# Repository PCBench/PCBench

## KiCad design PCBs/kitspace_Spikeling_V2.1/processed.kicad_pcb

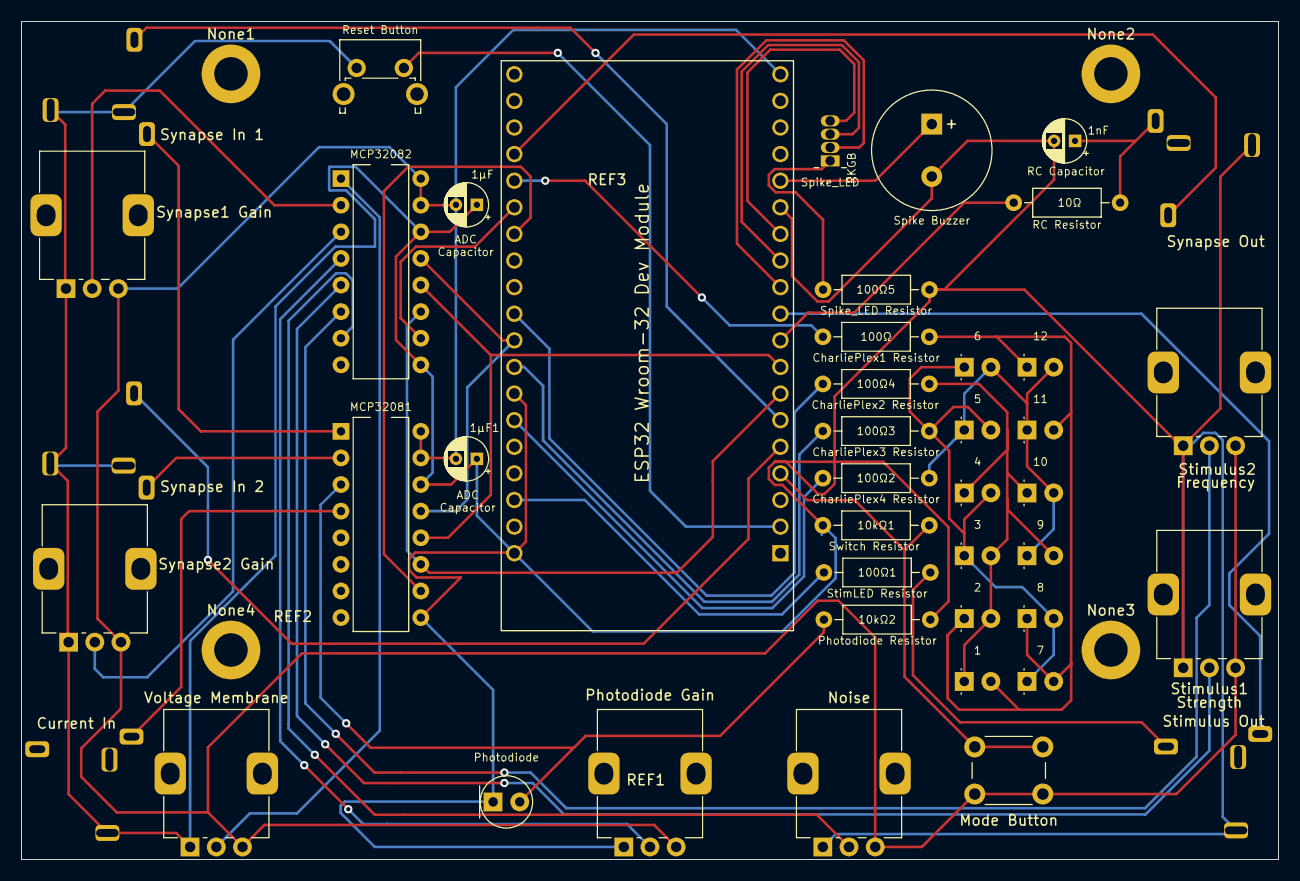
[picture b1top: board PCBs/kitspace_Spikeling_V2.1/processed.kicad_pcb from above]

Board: 2 copper layers, 120.0 x 80.0 mm, 51 parts (0 on the bottom side), 41 nets.

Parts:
1: D2; LED_D3.0mm
1nF: C3; CP_Radial_D4.0mm_P2.00mm
1μF, 1μF1: 1 μF; CP_Radial_D4.0mm_P2.00mm
2: D3; LED_D3.0mm
3: D4; LED_D3.0mm
4: D5; LED_D3.0mm
5: D6; LED_D3.0mm
6: D7; LED_D3.0mm
7: D8; LED_D3.0mm
8: LED; LED_D3.0mm
9: D10; LED_D3.0mm
10: D11; LED_D3.0mm
10kΩ1: R5; R_Axial_DIN0207_L6.3mm_D2.5mm_P10.16mm_Horizontal
10kΩ2: R2; R_Axial_DIN0207_L6.3mm_D2.5mm_P10.16mm_Horizontal
10Ω: R1; R_Axial_DIN0207_L6.3mm_D2.5mm_P10.16mm_Horizontal
11: D12; LED_D3.0mm
12: D13; LED_D3.0mm
100Ω: R6; R_Axial_DIN0207_L6.3mm_D2.5mm_P10.16mm_Horizontal
100Ω1: R3; R_Axial_DIN0207_L6.3mm_D2.5mm_P10.16mm_Horizontal
100Ω2: R9; R_Axial_DIN0207_L6.3mm_D2.5mm_P10.16mm_Horizontal
100Ω3: R8; R_Axial_DIN0207_L6.3mm_D2.5mm_P10.16mm_Horizontal
100Ω4: R7; R_Axial_DIN0207_L6.3mm_D2.5mm_P10.16mm_Horizontal
100Ω5: R4; R_Axial_DIN0207_L6.3mm_D2.5mm_P10.16mm_Horizontal
Current In: J4; Spikeling Audio Jack 3.5mm
ESP32 Wroom-32 Dev Module: ESP32-DEVKITC-32D; MODULE_ESP32-DEVKITC-32D
MCP32081: MCP32082; DIP-16_W7.62mm
MCP32082: MCP32084; DIP-16_W7.62mm
Mode Button: SW1; SW_PUSH_6mm_H13mm
Noise: RV4; Spikeling Potentiometer
None1, None3, None4: MountingHole_3.2mm_M3_DIN965_Pad
None2: MountingHole_M3; MountingHole_3.2mm_M3_DIN965_Pad
Photodiode: D1; LED_D5.0mm
Photodiode Gain: RV5; Spikeling Potentiometer
REF1: Spikeling_neuron; Spikeling_Photoreceptor
REF2: Spikeling_neuron; Spikeling_Electrode
REF3: Spikeling_neuron; Spikeling_Neuron
Reset Button: SW2; Spikeling reset button
Spike Buzzer: BZ1; Buzzer_11.5x9.5RM5
Spike_LED: RGB; LED_D5.0mm-4_RGB
Stimulus1: RV6; Spikeling Potentiometer
Stimulus2: RV7; Spikeling Potentiometer
Stimulus Out: J5; Spikeling Audio Jack 3.5mm
Synapse1 Gain: RV1; Spikeling Potentiometer
Synapse2 Gain: RV2; Spikeling Potentiometer
Synapse In 1: J2; Spikeling Audio Jack 3.5mm
Synapse In 2: J3; Spikeling Audio Jack 3.5mm
Synapse Out: J1; Spikeling Audio Jack 3.5mm
Voltage Membrane: RV3; Spikeling Potentiometer

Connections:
/00: ESP32 Wroom-32 Dev Module.33, MCP32082.10
/02: 100Ω.1, ESP32 Wroom-32 Dev Module.34
/04: ESP32 Wroom-32 Dev Module.32, MCP32081.10
/05: 100Ω4.1, ESP32 Wroom-32 Dev Module.29
/12: ESP32 Wroom-32 Dev Module.13, Spike_LED.4
/13: ESP32 Wroom-32 Dev Module.15, Spike Buzzer.1
/14: ESP32 Wroom-32 Dev Module.12, Spike_LED.3
/15: ESP32 Wroom-32 Dev Module.35, Synapse Out.T
/18: ESP32 Wroom-32 Dev Module.28, MCP32081.13, MCP32082.13
/19: 100Ω3.1, ESP32 Wroom-32 Dev Module.27
/21: 100Ω2.1, ESP32 Wroom-32 Dev Module.25
/22: 100Ω1.1, ESP32 Wroom-32 Dev Module.22
/25: 10Ω.1, ESP32 Wroom-32 Dev Module.9
/26: ESP32 Wroom-32 Dev Module.10, Stimulus Out.R
/27: ESP32 Wroom-32 Dev Module.11, Spike_LED.1
/32: ESP32 Wroom-32 Dev Module.7, MCP32081.11, MCP32082.11
/33: ESP32 Wroom-32 Dev Module.8, MCP32081.12, MCP32082.12
/34: ESP32 Wroom-32 Dev Module.5, Synapse In 2.T
/35: ESP32 Wroom-32 Dev Module.6, Synapse In 1.T
/39: 10kΩ1.1, ESP32 Wroom-32 Dev Module.4, Mode Button.1
/100: MCP32082.1, Voltage Membrane.2
/101: MCP32082.2, Synapse1 Gain.2
/102: MCP32082.3, Synapse2 Gain.2
/103: MCP32082.4, Photodiode Gain.2
/104: MCP32082.5, Stimulus1.2
/105: MCP32082.6, Stimulus2.2
/106: MCP32082.7, Noise.2
/200: MCP32081.1, Synapse In 1.R
/201: MCP32081.2, Synapse In 2.R
/202: 10kΩ2.1, MCP32081.3, Photodiode.2
/203: Current In.R, MCP32081.4
GNDREF: 1nF.2, 1μF.1, 1μF1.1, 10kΩ1.2, 10kΩ2.2, 100Ω5.1, Current In.S, ESP32 Wroom-32 Dev Module.14, ESP32 Wroom-32 Dev Module.20, ESP32 Wroom-32 Dev Module.26, MCP32081.9, MCP32081.14, MCP32082.9, MCP32082.14, Noise.1, Photodiode.1, Photodiode Gain.1, Reset Button.1, Spike Buzzer.2, Stimulus1.1, Stimulus2.1, Stimulus Out.S, Synapse1 Gain.1, Synapse2 Gain.1, Synapse In 1.S, Synapse In 2.S, Synapse Out.S, Voltage Membrane.1
unnamed: 1nF.1, 10Ω.2, Synapse Out.R
unnamed: 1.2, 2.1, 7.2, 8.1, 11.2, 12.1, 100Ω.2
unnamed: 1.1, 2.2, 3.2, 4.1, 9.2, 10.1, 100Ω4.2
unnamed: 3.1, 4.2, 5.2, 6.1, 7.1, 8.2, 100Ω3.2
unnamed: 5.1, 6.2, 9.1, 10.2, 11.1, 12.2, 100Ω2.2
unnamed: 100Ω5.2, Spike_LED.2
unnamed: 100Ω1.2, Stimulus Out.T
unnamed: ESP32 Wroom-32 Dev Module.2, Reset Button.2
VCC: 1μF.2, 1μF1.2, ESP32 Wroom-32 Dev Module.19, MCP32081.15, MCP32081.16, MCP32082.15, MCP32082.16, Mode Button.2, Noise.3, Photodiode Gain.3, Stimulus1.3, Stimulus2.3, Synapse1 Gain.3, Synapse2 Gain.3, Voltage Membrane.3

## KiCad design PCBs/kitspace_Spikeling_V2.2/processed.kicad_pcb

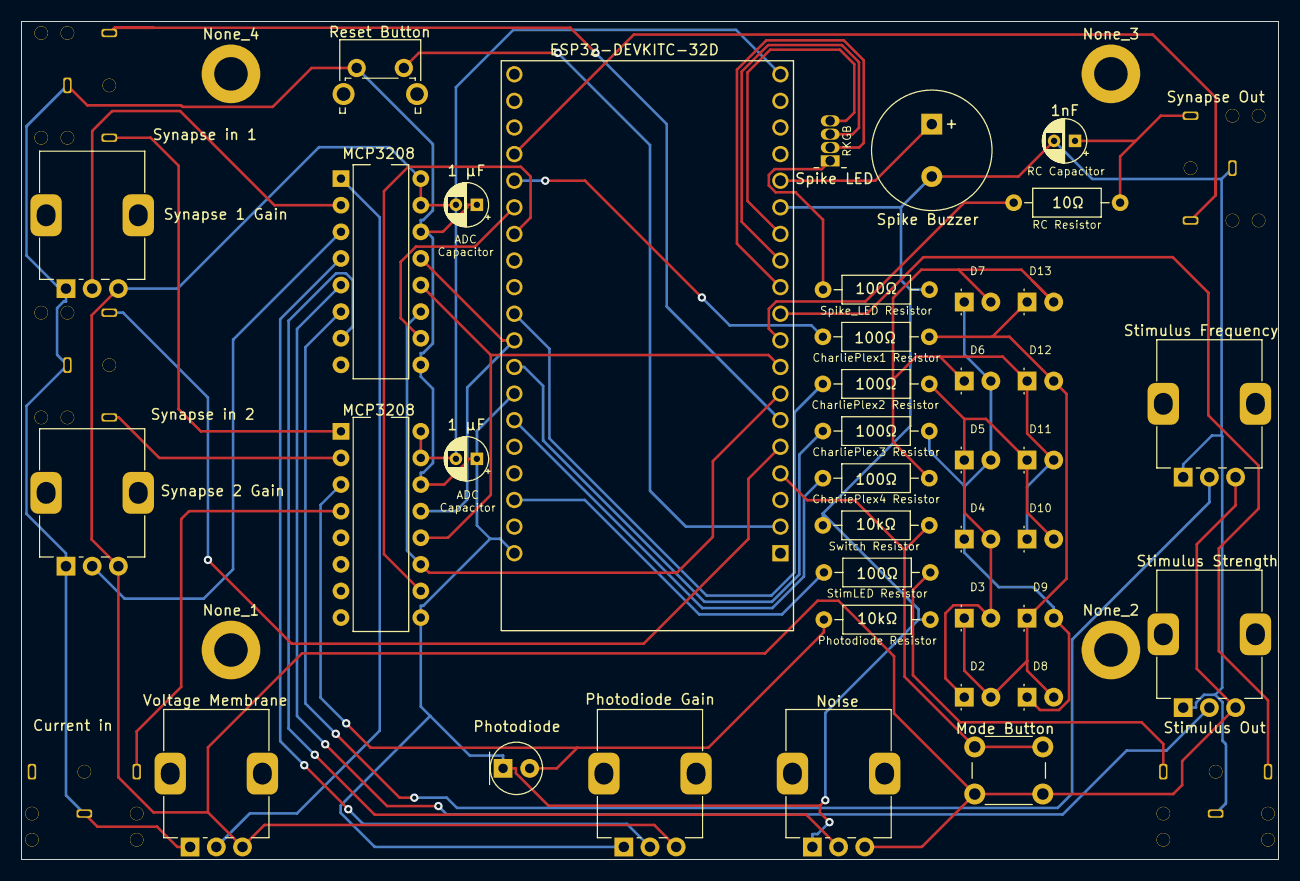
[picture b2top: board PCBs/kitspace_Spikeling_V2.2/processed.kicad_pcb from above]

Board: 2 copper layers, 120.0 x 80.0 mm, 48 parts (0 on the bottom side), 41 nets.

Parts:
BZ1: Spike Buzzer; Buzzer_11.5x9.5RM5
C1, C2: 1 μF; CP_Radial_D4.0mm_P2.00mm
C3: 1nF; CP_Radial_D4.0mm_P2.00mm
D1: Photodiode; LED_D5.0mm
D2: Mode1; LED_D3.0mm
D3: Mode2; LED_D3.0mm
D4: Mode3; LED_D3.0mm
D5: Mode4; LED_D3.0mm
D6: Mode5; LED_D3.0mm
D7: Mode6; LED_D3.0mm
D8: Mode7; LED_D3.0mm
D9: Mode8; LED_D3.0mm
D10: Mode9; LED_D3.0mm
D11: Mode10; LED_D3.0mm
D12: Mode11; LED_D3.0mm
D13: Mode12; LED_D3.0mm
D14: Spike LED; LED_D5.0mm-4_RGB
J1: Synapse Out; Spikeling Audio Jack 3.5mm
J2: Synapse in 1; Spikeling Audio Jack 3.5mm
J3: Synapse in 2; Spikeling Audio Jack 3.5mm
J4: Current in; Spikeling Audio Jack 3.5mm
J5: Stimulus Out; Spikeling Audio Jack 3.5mm
None_1, None_2, None_4: MountingHole_3.2mm_M3_DIN965_Pad
None_3: MountingHole_M3; MountingHole_3.2mm_M3_DIN965_Pad
R1: 10Ω; R_Axial_DIN0207_L6.3mm_D2.5mm_P10.16mm_Horizontal
R2, R5: 10kΩ; R_Axial_DIN0207_L6.3mm_D2.5mm_P10.16mm_Horizontal
R3, R4, R6, R7, R8, R9: 100Ω; R_Axial_DIN0207_L6.3mm_D2.5mm_P10.16mm_Horizontal
RV1: Synapse 1 Gain; Spikeling Potentiometer
RV2: Synapse 2 Gain; Spikeling Potentiometer
RV3: Voltage Membrane; Spikeling Potentiometer
RV4: Noise; Spikeling Potentiometer
RV5: Photodiode Gain; Spikeling Potentiometer
RV6: Stimulus Strength; Spikeling Potentiometer
RV7: Stimulus Frequency; Spikeling Potentiometer
SW1: Mode Button; SW_PUSH_6mm_H13mm
SW2: Reset Button; Spikeling reset button
U1: ESP32-DEVKITC-32D; MODULE_ESP32-DEVKITC-32D
U2, U3: MCP3208; DIP-16_W7.62mm

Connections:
/00: U1.33, U2.10
/02: R6.1, U1.34
/04: U1.32, U3.10
/05: R7.1, U1.29
/12: D14.4, U1.13
/13: BZ1.1, U1.15
/14: D14.3, U1.12
/15: J1.T, U1.35
/18: U1.28, U2.13, U3.13
/19: R8.1, U1.27
/21: R9.1, U1.25
/22: R3.1, U1.22
/25: R1.1, U1.9
/26: J5.R, U1.10
/27: D14.1, U1.11
/32: U1.7, U2.11, U3.11
/33: U1.8, U2.12, U3.12
/34: J3.T, U1.5
/35: J2.T, U1.6
/39: R5.1, SW1.1, U1.4
/100: RV3.2, U2.1
/101: RV1.2, U2.2
/102: RV2.2, U2.3
/103: RV5.2, U2.4
/104: RV6.2, U2.5
/105: RV7.2, U2.6
/106: RV4.2, U2.7
/200: J2.R, U3.1
/201: J3.R, U3.2
/202: D1.2, R2.1, U3.3
/203: J4.R, U3.4
GNDREF: BZ1.2, C1.1, C2.1, C3.2, D1.1, J1.S, J2.S, J3.S, J4.S, J5.S, R2.2, R4.1, R5.2, RV1.1, RV2.1, RV3.1, RV4.1, RV5.1, RV6.1, RV7.1, SW2.1, U1.14, U1.20, U1.26, U2.9, U2.14, U3.9, U3.14
unnamed: C3.1, J1.R, R1.2
unnamed: J5.T, R3.2
unnamed: D14.2, R4.2
unnamed: D2.2, D3.1, D8.2, D9.1, D12.2, D13.1, R6.2
unnamed: D2.1, D3.2, D4.2, D5.1, D10.2, D11.1, R7.2
unnamed: D4.1, D5.2, D6.2, D7.1, D8.1, D9.2, R8.2
unnamed: D6.1, D7.2, D10.1, D11.2, D12.1, D13.2, R9.2
unnamed: SW2.2, U1.2
VCC: C1.2, C2.2, RV1.3, RV2.3, RV3.3, RV4.3, RV5.3, RV6.3, RV7.3, SW1.2, U1.19, U2.15, U2.16, U3.15, U3.16

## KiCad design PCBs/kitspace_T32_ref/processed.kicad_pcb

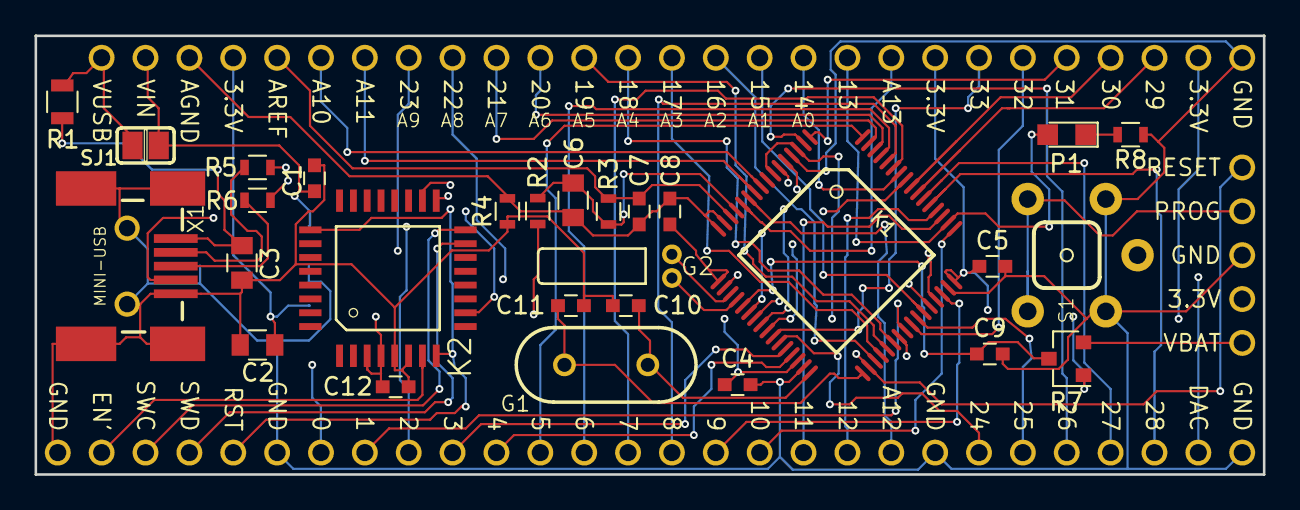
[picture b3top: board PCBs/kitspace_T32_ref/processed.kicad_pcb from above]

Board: 4 copper layers, 71.1 x 25.4 mm, 89 parts (1 on the bottom side), 66 nets.

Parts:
C1, C4, C5, C7, C8, C9, C12: 0.1uF; C_0603
C2, C3, C6: 2.2uF; C_0805
C10, C11: 22pF; C_0603
G1: 16MHz; HC49US
G2: 32.768kHz; TC26H
K1: MK20DX256VLH7; LQFP64-05
K2: MKL04Z32VLC4; LQFP32-08
P1: LED_0805
R1: FUSE; R_0805
R2, R4: R_0603
R3, R8: 470R; R_0603
R5, R6: 33R; R_0603
R7: SOT-23
S1: ALPS_SKHH
SJ1: SOLDERJUMPER
SX1, SX2, SX3, SX4, SX5, SX6, SX7, SX8, SX9, SX10, SX11, SX12, SX13, SX14, SX15, SX16, SX17, SX18, SX19, SX20, SX21, SX22, SX23, SX24, SX25, SX26, SX27, SX28, SX29, SX30, SX31, SX32, SX33, SX34, SX35, SX36, SX37, SX38, SX39, SX40, SX41, SX42, SX43, SX44, SX45, SX46, SX47, SX48, SX49, SX50, SX51, SX52, SX53, SX54, SX55, SX56, SX57, SX58, SX59, SX60: PIN; PTH_39MIL
T1: MCP1825S; SOT-223
X1: MINI-USB; MOLEX_SD-67503-010

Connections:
/N$1: K2.7, SX59.1
/N$2: K1.22, K2.16, SX58.1
/N$3: K1.24, K2.17
/N$5: C10.1, G1.1, K1.32
/N$6: C11.1, G1.2, K1.33
/N$7: G2.2, K1.19
/N$8: G2.1, K1.20
/N$9: K2.18, S1.1, S1.2, SX40.1
/N$10: K1.5, R6.2
/N$11: C8.1, K1.17
/N$12: K1.34, K2.8, K2.25, SX38.1, SX56.1
/N$13: C7.1, K1.14, R3.2, SX16.1
/N$14: K1.6, R5.2
/N$15: C6.1, K1.13, R2.1, R3.1
/N$16: R6.1, X1.3
/N$17: R5.1, X1.2
/N$18: C3.1, R1.1, X1.1
/N$19: K1.23, K2.10, X1.4
/N$21: K1.45, SX5.1
/N$22: K1.44, SX6.1
/N$23: K1.63, SX7.1
/N$24: K1.62, SX8.1
/N$25: K1.37, SX9.1
/N$26: K1.38, SX10.1
/N$27: K1.36, SX11.1
/N$28: K1.35, SX13.1
/N$29: K1.43, SX15.1
/N$30: K1.58, SX17.1
/N$31: K1.50, P1.2, SX18.1
/N$32: K1.52, SX19.1
/N$33: K1.51, SX20.1
/N$34: K1.49, SX21.1
/N$35: K1.46, SX22.1
/N$36: K1.60, SX23.1
/N$37: K1.59, SX24.1
/N$38: K1.61, SX25.1
/N$39: K1.64, SX26.1
/N$40: K1.29, SX27.1
/N$41: K1.28, SX28.1
/N$42: K1.57, SX29.1
/N$43: K1.40, SX30.1
/N$44: K1.39, SX31.1
/N$45: K1.12, SX33.1
/N$46: K1.26, SX35.1
/N$47: K1.41, SX36.1
/N$48: K1.1, SX37.1
/N$49: K1.56, SX39.1
/N$50: K1.55, SX41.1
/N$51: K1.53, SX43.1
/N$52: P1.1, R8.2
/N$53: C6.2, C7.2, C8.2, K1.15, K1.16, R4.2, SX3.1
/N$54: K1.18, SX52.1
/N$55: K1.11, SX51.1
/N$57: K1.27, SX49.1
/N$58: K1.42, SX48.1
/N$59: K1.2, SX47.1
/N$60: K1.54, SX45.1
/N$61: C1.1, SJ1.2, SX2.1, T1.1
/N$63: R7.2, SX46.1
/N$64: K1.10, SX12.1
/N$65: K1.9, SX14.1
/N$67: R1.2, SJ1.1, SX1.1
/N$68: C9.1, K1.21, R7.3
/N$69: C2.1, C4.1, C5.1, C12.1, K1.3, K1.7, K1.30, K1.48, K2.3, K2.4, R2.2, R7.1, SX4.1, SX34.1, SX44.1, SX54.1, T1.3
/N$70: K1.25, K2.15, SX57.1
GND: C1.2, C2.2, C3.2, C4.2, C5.2, C9.2, C10.2, C11.2, C12.2, K1.4, K1.31, K1.47, K2.5, K2.6, R4.1, R8.1, S1.3, S1.4, SX32.1, SX42.1, SX50.1, SX53.1, SX55.1, SX60.1, T1.2, T1.4, X1.5, X1.P$1, X1.P$2, X1.P$3, X1.P$4, X1.P$5, X1.P$6

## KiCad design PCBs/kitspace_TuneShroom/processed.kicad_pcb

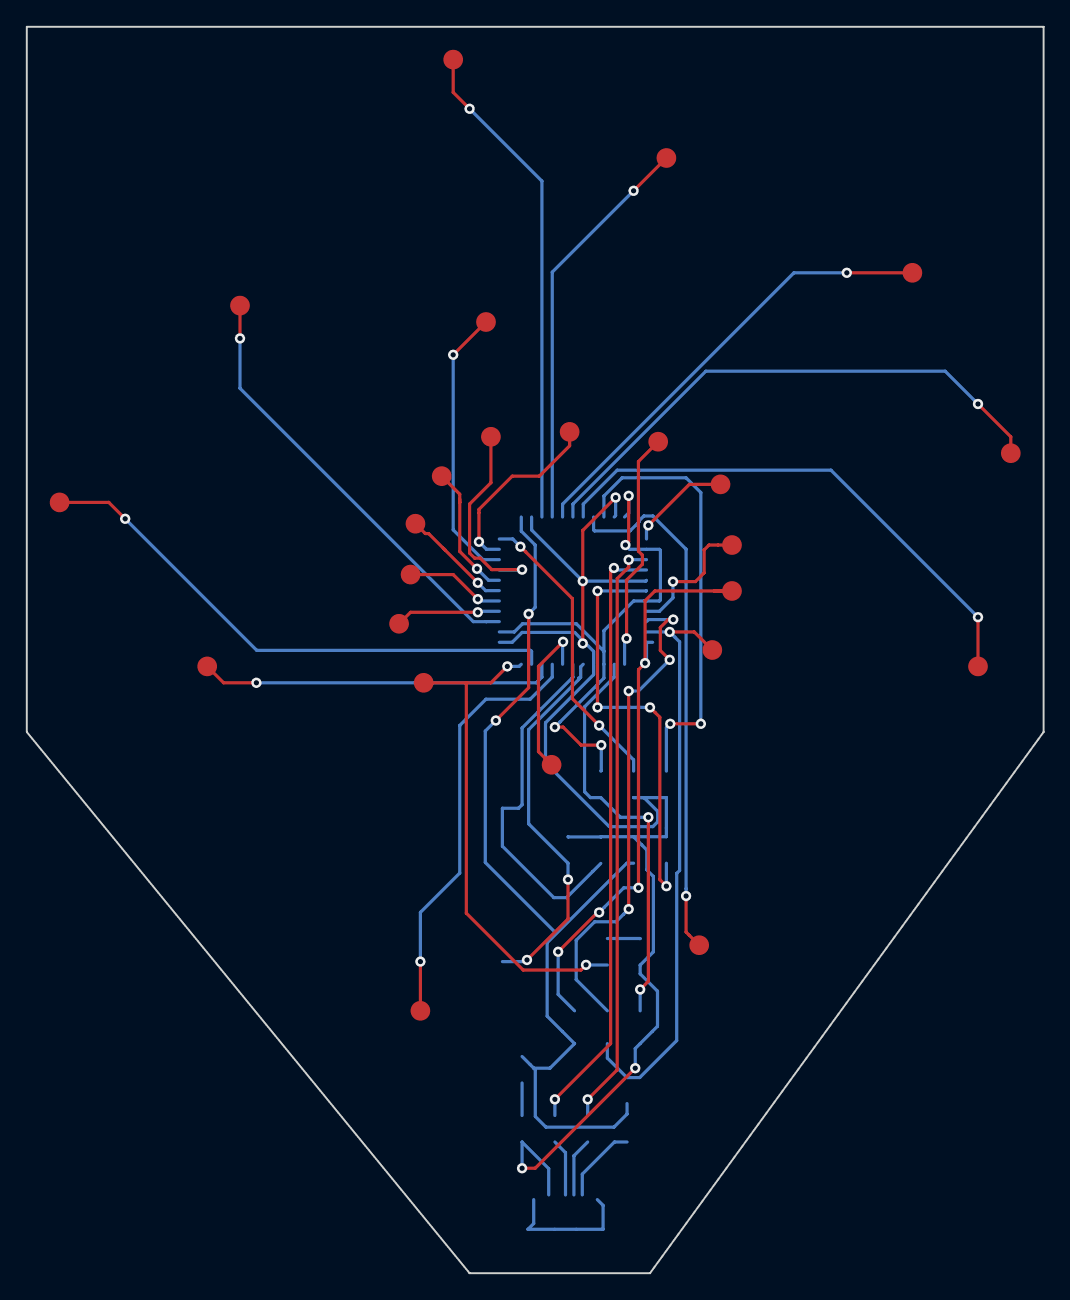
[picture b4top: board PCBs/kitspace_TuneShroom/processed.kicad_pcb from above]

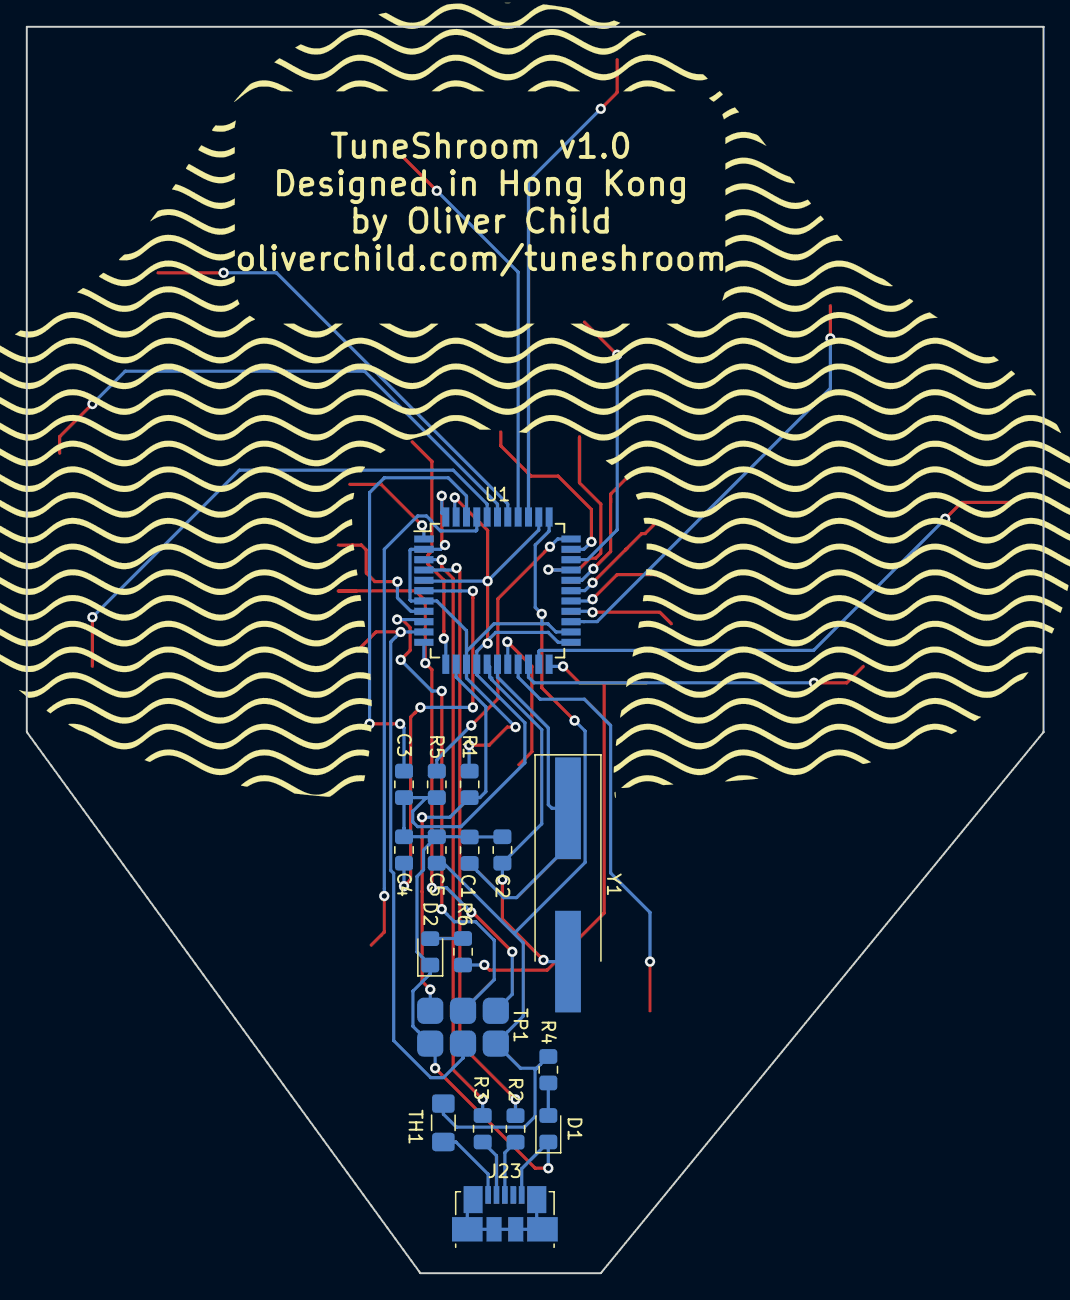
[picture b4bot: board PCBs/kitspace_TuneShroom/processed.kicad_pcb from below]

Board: 2 copper layers, 78.7 x 96.5 mm, 42 parts (18 on the bottom side), 40 nets.

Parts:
C1, C2: 22pF; C_0805_2012Metric_Pad1.15x1.40mm_HandSolder
C3, C5: 0.1uF; C_0805_2012Metric_Pad1.15x1.40mm_HandSolder
C4: 1uF; C_0805_2012Metric_Pad1.15x1.40mm_HandSolder
D1, D2: LED; LED_0805_2012Metric_Pad1.15x1.40mm_HandSolder
J1, J2, J3, J4, J5, J6, J7, J8, J9, J10, J11, J12, J13, J14, J15, J16, J17, J18, J19, J20, J21, J22, J24, J25: Conn_01x01; contact
J23: USB_B_Micro; USB_Micro-B_Molex_47346-0001
R1, R5: 10K; R_0805_2012Metric_Pad1.15x1.40mm_HandSolder
R2, R3: 22; R_0805_2012Metric_Pad1.15x1.40mm_HandSolder
R4, R6: 330; R_0805_2012Metric_Pad1.15x1.40mm_HandSolder
TH1: Thermistor; Fuse_1206_3216Metric_Pad1.42x1.75mm_HandSolder
TP1: ICSP
U1: ATmega32U4-AU; TQFP-44_10x10mm_P0.8mm
Y1: 16MHz; Crystal_SMD_HC49-SD_HandSoldering

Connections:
+5V: C5.1, R1.1, R4.1, TH1.1, TP1.2, U1.2, U1.7, U1.14, U1.24, U1.34, U1.44
A0: J1.1, U1.36
A1: J3.1, U1.37
A2: J5.1, U1.38
A3: J7.1, U1.39
A4: J9.1, U1.40
A5: J11.1, U1.41
D0: J13.1, U1.20
D1: J15.1, U1.21
D2: J17.1, U1.19
D3: J19.1, U1.18
D4: J21.1, U1.25
D5: J2.1, U1.31
D6: J4.1, U1.27
D7: J6.1, U1.1
D8: J8.1, U1.28
D9: J10.1, U1.29
D10: J12.1, U1.30
D11: J14.1, U1.12
D12: J16.1, U1.26
D13: J18.1, U1.32
D17: J20.1, U1.8
D+: R2.1, U1.4
D-: R3.1, U1.3
GND: C1.2, C2.2, C3.2, C4.2, C5.2, D1.1, D2.1, J23.5, R5.2, TP1.6, U1.5, U1.15, U1.23, U1.35, U1.43
MISO: J22.1, TP1.1, U1.11
MOSI: J24.1, TP1.4, U1.10
unnamed: C1.1, U1.17, Y1.1
unnamed: C2.1, U1.16, Y1.2
unnamed: C3.1, U1.42
unnamed: C4.1, U1.6
unnamed: D1.2, R4.2
unnamed: D2.2, R6.2
unnamed: J23.1, TH1.2
unnamed: J23.2, R3.2
unnamed: J23.3, R2.2
unnamed: R5.1, U1.33
RESET: R1.2, TP1.5, U1.13
RX_LED: J25.1, R6.1, U1.22
SCK: TP1.3, U1.9

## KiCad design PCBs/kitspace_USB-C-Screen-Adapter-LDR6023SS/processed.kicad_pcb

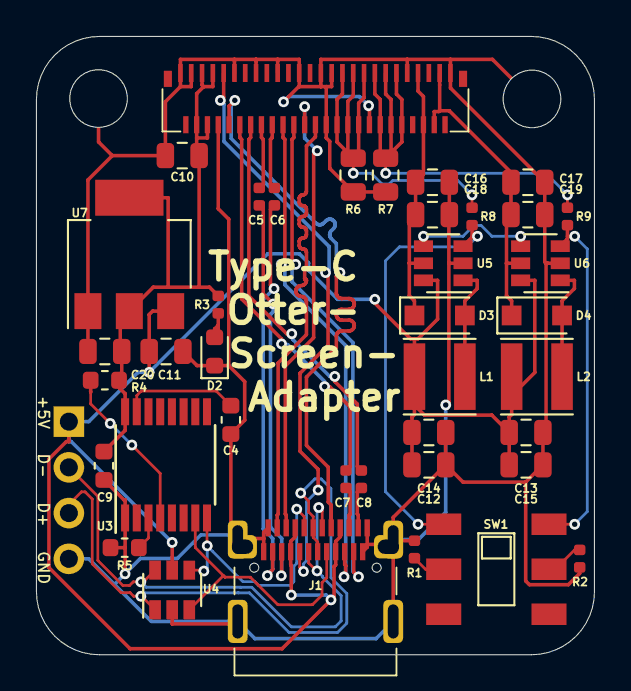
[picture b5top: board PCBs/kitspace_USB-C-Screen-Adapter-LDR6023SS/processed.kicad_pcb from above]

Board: 2 copper layers, 31.0 x 34.3 mm, 42 parts (0 on the bottom side), 36 nets.

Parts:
C4, C9: 100n; C_0603_1608Metric
C5, C6, C7, C8: 100n; C_0402_1005Metric
C10, C11, C12, C13, C14, C15, C16, C17, C18, C19, C20: 2.2uF; C_0805_2012Metric
D2: LED; LED_0603_1608Metric
D3, D4: SM4007PL; D_SOD-123F
H1, H2: MountingHole_Pad; MountingHole_3.2mm_M3
J1: USB_C_Receptacle; USB_C_24P_SMD
J2: USB; PinHeader_1x04_P2.54mm_Vertical
L1, L2: 22uH; L_Taiyo-Yuden_MD-4040
R1, R2, R3, R8, R9: 1k; R_0402_1005Metric
R4, R5: 10k; R_0603_1608Metric
R6, R7: 1.6; R_0805_2012Metric
SW1: BRIGHTNESS; K3-2235S-K1
U2: 5022505191
U3: LDR6023SS; TSSOP-16_4.4x5mm_P0.65mm
U4: USBLC6-4; SOT-23-6
U5, U6: SY7200AABC; SOT-23-6
U7: AMS1117-3.3; SOT-223-3_TabPin2

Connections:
+3V3: C9.1, C10.1, C20.1, R3.2, R4.2, U2.4, U2.5, U2.6, U2.7, U3.16, U7.2
+5V: C11.1, C12.1, C13.1, C14.1, C15.1, J1.A4, J1.A9, J1.B4, J1.B9, J2.1, L1.1, L2.1, U4.5, U5.6, U6.6, U7.3
/_L0_N: C7.2, J1.A10
/_L0_P: C8.2, J1.A11
/_L1_N: C5.2, J1.B10
/_L1_P: C6.2, J1.B11
AUX_N: J1.A8, U2.10
AUX_P: J1.B8, U2.9
CC1: J1.A5, U3.8, U4.4
CC2: J1.B5, U3.7, U4.3
GND: C4.2, C9.2, C10.2, C11.2, C12.2, C13.2, C14.2, C15.2, C16.2, C17.2, C18.2, C19.2, C20.2, D2.1, H1.1, H2.1, J1.A1, J1.A12, J1.B1, J1.B12, J1.S1, J2.4, R1.1, R2.1, R5.2, R6.2, R7.2, U2.1, U2.3, U2.8, U2.11, U2.15, U2.19, U2.23, U2.27, U2.28, U2.29, U2.36, U2.43, U2.51, U3.1, U4.2, U5.2, U6.2, U7.1
L0_N: C7.1, U2.12
L0_P: C8.1, U2.14
L1_N: C5.1, U2.16
L1_P: C6.1, U2.18
L2_N: J1.B3, U2.20
L2_P: J1.B2, U2.22
L3_N: J1.A3, U2.24
L3_P: J1.A2, U2.26
LEDA1: C17.1, C19.1, D4.1, U2.48, U2.49, U6.5
LEDA2: C16.1, C18.1, D3.1, U2.45, U2.46, U5.5
LEDC1: R7.1, R9.2, U2.37, U2.38, U2.39, U2.40, U2.41, U2.42
LEDC1DIM: R9.1, SW1.4, U6.3
LEDC2: R6.1, R8.2, U2.30, U2.31, U2.32, U2.33, U2.34, U2.35
LEDC2DIM: R8.1, SW1.1, U5.3
unnamed: C4.1, U3.15
unnamed: D2.2, R3.1
unnamed: D3.2, L1.2, U5.1
unnamed: D4.2, L2.2, U6.1
unnamed: R1.2, SW1.2
unnamed: R2.2, SW1.5
unnamed: R4.1, U3.4
unnamed: R5.1, U3.3
PWM: U5.4, U6.4
USB_N: J1.A7, J1.B7, J2.2, U4.6
USB_P: J1.A6, J1.B6, J2.3, U4.1

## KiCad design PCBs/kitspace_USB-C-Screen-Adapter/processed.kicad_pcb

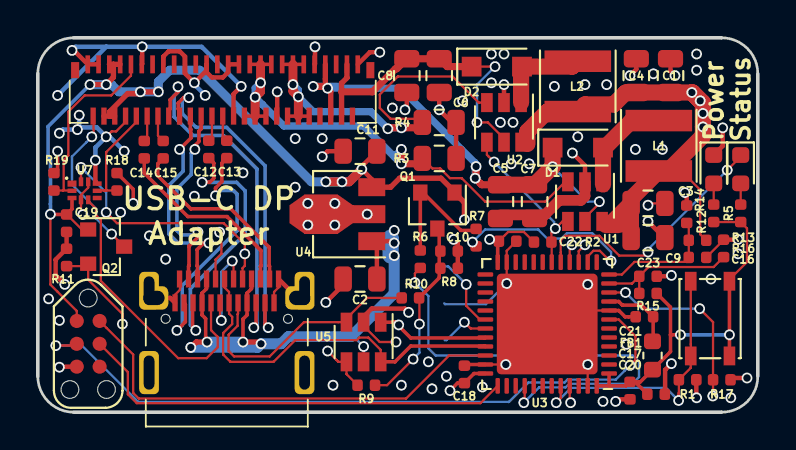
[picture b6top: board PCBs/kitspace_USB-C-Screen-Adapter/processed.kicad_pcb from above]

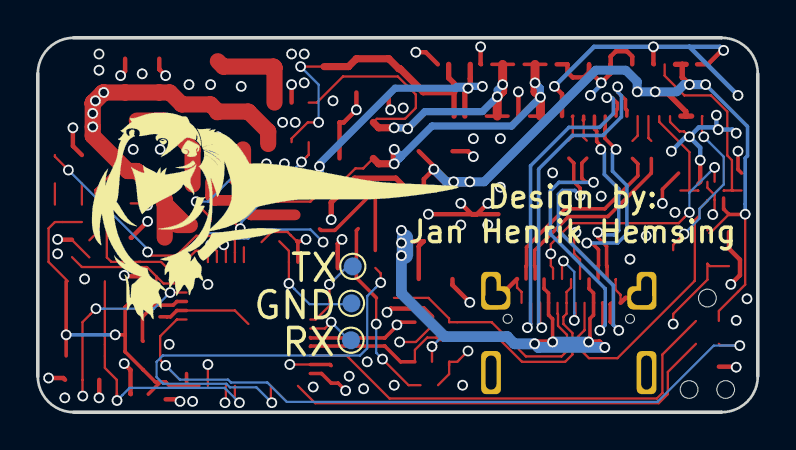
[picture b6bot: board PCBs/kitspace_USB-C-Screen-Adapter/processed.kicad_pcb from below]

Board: 4 copper layers, 40.0 x 20.8 mm, 64 parts (3 on the bottom side), 51 nets.

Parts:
C1, C2, C3, C4, C5, C6, C7, C8, C9, C11: 2.2uF; C_0805_2012Metric
C10: 820p; C_0402_1005Metric
C12, C13, C14, C15, C16, C17, C18, C19, C20, C21, C22: 100n; C_0402_1005Metric
C23: 220n; C_0402_1005Metric
D1, D2: SM4007PL; D_SOD-123F
D3, D4: LED; LED_0603_1608Metric
FB1: FERRET; L_0603_1608Metric
J1: USB_C_Receptacle; USB_C_24P_SMD
L1, L2: 22uH; L_Taiyo-Yuden_MD-4040
P1: TC2030-CTX-Tag-Connect; TC2030
Q1, Q2: 2N7002; SOT-23
R1, R2, R8: 5k1; R_0402_1005Metric
R3, R4: 0.8; R_0805_2012Metric
R5, R12: 1k; R_0402_1005Metric
R6: 169; R_0402_1005Metric
R7: 75; R_0402_1005Metric
R9, R10, R18, R19: 0; R_0402_1005Metric
R11: 1M; R_0402_1005Metric
R13: 8k2; R_0402_1005Metric
R14: 1k5; R_0402_1005Metric
R15, R17: 24k; R_0402_1005Metric
R16: 4k7; R_0402_1005Metric
SW1: DFU; SW_SPST_PTS810
TP1: UART_TX; TestPoint_Pad_D1.0mm
TP2: UART_RX; TestPoint_Pad_D1.0mm
TP3: GND; TestPoint_Pad_D1.0mm
U1, U2: SY7200AABC; SOT-23-6
U3: STM32F072CBUx; QFN-48-1EP_7x7mm_P0.5mm_EP5.6x5.6mm
U4: AP2204R-3.3; SOT-89-3
U5: USBLC6-4; SOT-23-6
U6: 5022505191
U7: STG3684A; QFN10L

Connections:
+3V3: C11.1, C17.1, C18.1, C19.1, C20.1, C22.1, FB1.2, P1.1, Q1.1, Q2.1, R2.1, R5.2, R12.2, R15.2, SW1.2, U3.1, U3.24, U3.36, U3.48, U4.3, U6.4, U6.5, U6.6, U6.7, U7.3
+5V: C1.1, C2.1, C3.1, C4.1, C9.1, J1.A4, J1.A9, J1.B4, J1.B9, L1.1, L2.1, R13.2, U1.6, U2.6, U4.1, U5.5
/_L0_N: C14.2, J1.A10
/_L0_P: C15.2, J1.A11
/_L3_N: C12.2, J1.B10
/_L3_P: C13.2, J1.B11
AUX_N: R18.1, U6.10, U7.7
AUX_P: R19.1, U6.9, U7.2
CC1: J1.A5, R9.1, U5.4
CC2: J1.B5, R10.1, U5.3
CC_RX: R7.2, U3.14
CC_TX: R6.2, U3.40
DFU: R1.2, SW1.1, U3.44
GND: C1.2, C2.2, C3.2, C4.2, C5.2, C6.2, C7.2, C8.2, C9.2, C10.2, C11.2, C16.2, C17.2, C18.2, C19.2, C20.2, C21.2, C22.2, C23.2, D4.1, J1.A1, J1.A12, J1.B1, J1.B12, J1.S1, P1.5, R1.1, R3.2, R4.2, R8.2, R11.1, R14.1, R16.1, R17.1, TP3.1, U1.2, U2.2, U3.8, U3.23, U3.35, U3.47, U3.49, U4.2, U5.2, U6.1, U6.3, U6.8, U6.11, U6.15, U6.19, U6.23, U6.27, U6.28, U6.29, U6.36, U6.43, U6.51, U7.8
HPD: Q2.3, U6.2
L0_N: C14.1, U6.12
L0_P: C15.1, U6.14
L1_N: J1.B3, U6.16
L1_P: J1.B2, U6.18
L2_N: J1.A3, U6.20
L2_P: J1.A2, U6.22
L3_N: C12.1, U6.24
L3_P: C13.1, U6.26
LEDA1: C6.1, C8.1, D2.1, U2.5, U6.48, U6.49
LEDA2: C5.1, C7.1, D1.1, U1.5, U6.45, U6.46
LEDC1: R4.1, U2.3, U6.37, U6.38, U6.39, U6.40, U6.41, U6.42
LEDC2: R3.1, U1.3, U6.30, U6.31, U6.32, U6.33, U6.34, U6.35
NRST: P1.3, U3.7
unnamed: C10.1, Q1.3, R8.1, R9.2, R10.2
unnamed: D1.2, L1.2, U1.1
unnamed: D2.2, L2.2, U2.1
unnamed: D3.1, U3.17
unnamed: D3.2, R5.1
unnamed: D4.2, R12.1
unnamed: Q1.2, R6.1, R7.1
unnamed: TP1.1, U3.30
unnamed: TP2.1, U3.31
PWM: R2.2, U1.4, U2.4, U3.18
RXREF: C23.1, R15.1, R16.2, U3.11
SBU1: J1.A8, U7.10
SBU2: J1.B8, U7.5
SBU_ENABLE: R17.2, U3.10, U7.4, U7.9
STM_HPD: Q2.2, R11.2, U3.45
SWCLK: P1.4, U3.37
SWDIO: P1.2, U3.34
USB_N: J1.A7, J1.B7, U3.32, U5.1
USB_P: J1.A6, J1.B6, U3.33, U5.6
VBUS_SENSE: C16.1, R13.1, R14.2, U3.12
VDDA: C21.1, FB1.1, U3.9
_DP_AUX_N: R18.2, U3.15
_DP_AUX_P: R19.2, U3.16
